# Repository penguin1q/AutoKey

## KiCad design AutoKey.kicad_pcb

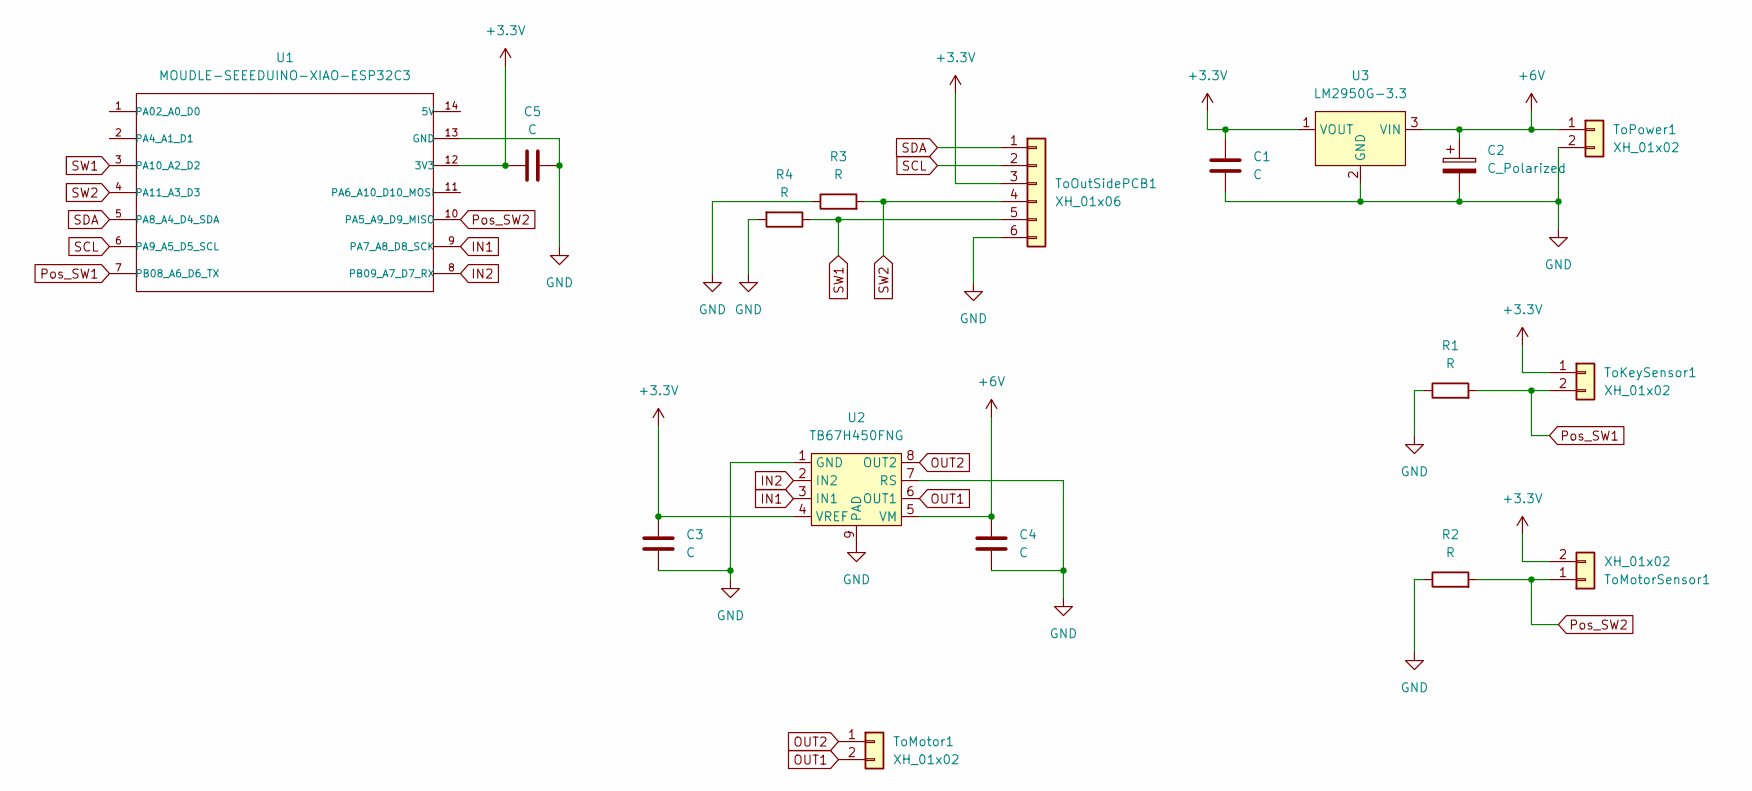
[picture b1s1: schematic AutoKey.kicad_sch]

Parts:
C1, C3, C4, C5: C; CP_EIA-1608-10_AVX-L_Pad1.25x1.05mm_HandSolder
C2: C_Polarized; CP_Radial_D5.0mm_P2.50mm
R1, R2, R3, R4: R; R_0603_1608Metric_Pad0.98x0.95mm_HandSolder
ToKeySensor1: XH_01x02; JST_XH_S2B-XH-A_1x02_P2.50mm_Horizontal
ToMotor1: XH_01x02; JST_XH_S2B-XH-A_1x02_P2.50mm_Horizontal
ToMotorSensor1: XH_01x02; JST_XH_S2B-XH-A_1x02_P2.50mm_Horizontal
ToOutSidePCB1: XH_01x06; JST_XH_S6B-XH-A_1x06_P2.50mm_Horizontal
ToPower1: XH_01x02; JST_XH_S2B-XH-A_1x02_P2.50mm_Horizontal
U1: MOUDLE-SEEEDUINO-XIAO-ESP32C3; MOUDLE14P-SMD-2.54-21X17.8MM
U2: TB67H450FNG; HSOP-8-1EP_3.9x4.9mm_P1.27mm_EP2.3x2.3mm_ThermalVias
U3: LM2950G-3.3; TO-92_Inline

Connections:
+3.3V: C1.2, C3.2, C5.2, ToKeySensor1.1, ToMotorSensor1.2, ToOutSidePCB1.3, U1.12 (3V3), U2.4 (VREF), U3.1 (VOUT)
+6V: C2.1, C4.2, ToPower1.1, U2.5 (VM), U3.3 (VIN)
GND: C1.1, C2.2, C3.1, C4.1, C5.1, R1.1, R2.1, R3.1, R4.2, ToOutSidePCB1.6, ToPower1.2, U1.13 (GND), U2.1 (GND), U2.7 (RS), U2.9 (PAD), U3.2 (GND)
IN1: U1.9 (PA7_A8_D8_SCK), U2.3 (IN1)
IN2: U1.8 (PB09_A7_D7_RX), U2.2 (IN2)
OUT1: ToMotor1.2, U2.6 (OUT1)
OUT2: ToMotor1.1, U2.8 (OUT2)
Pos_SW1: R1.2, ToKeySensor1.2, U1.7 (PB08_A6_D6_TX)
Pos_SW2: R2.2, ToMotorSensor1.1, U1.10 (PA5_A9_D9_MISO)
SCL: ToOutSidePCB1.2, U1.6 (PA9_A5_D5_SCL)
SDA: ToOutSidePCB1.1, U1.5 (PA8_A4_D4_SDA)
SW1: R4.1, ToOutSidePCB1.5, U1.3 (PA10_A2_D2)
SW2: R3.2, ToOutSidePCB1.4, U1.4 (PA11_A3_D3)

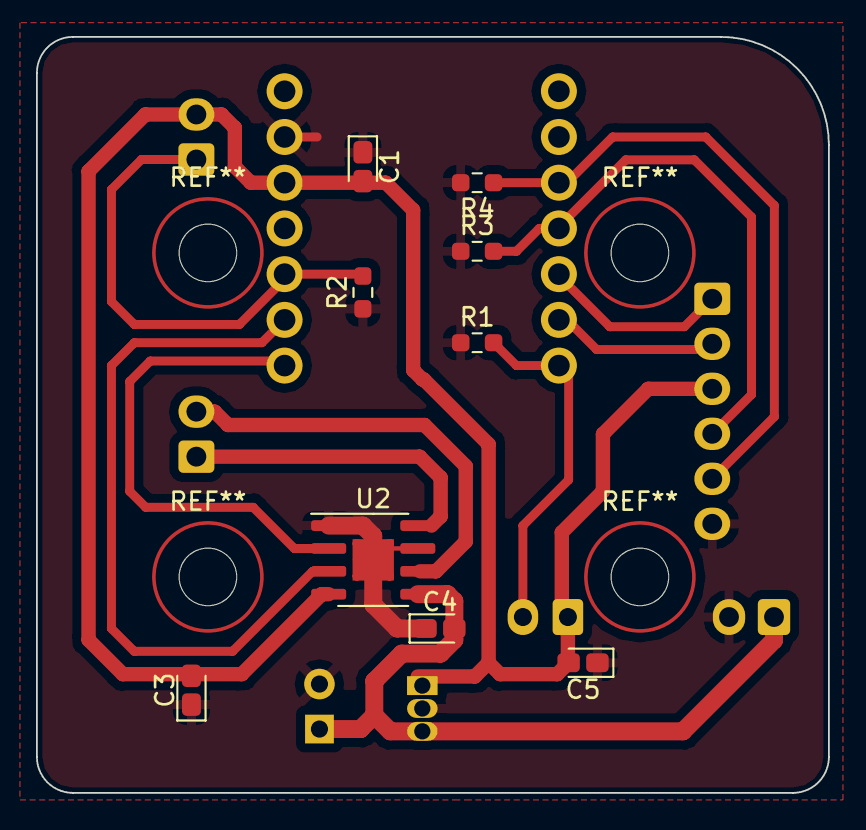
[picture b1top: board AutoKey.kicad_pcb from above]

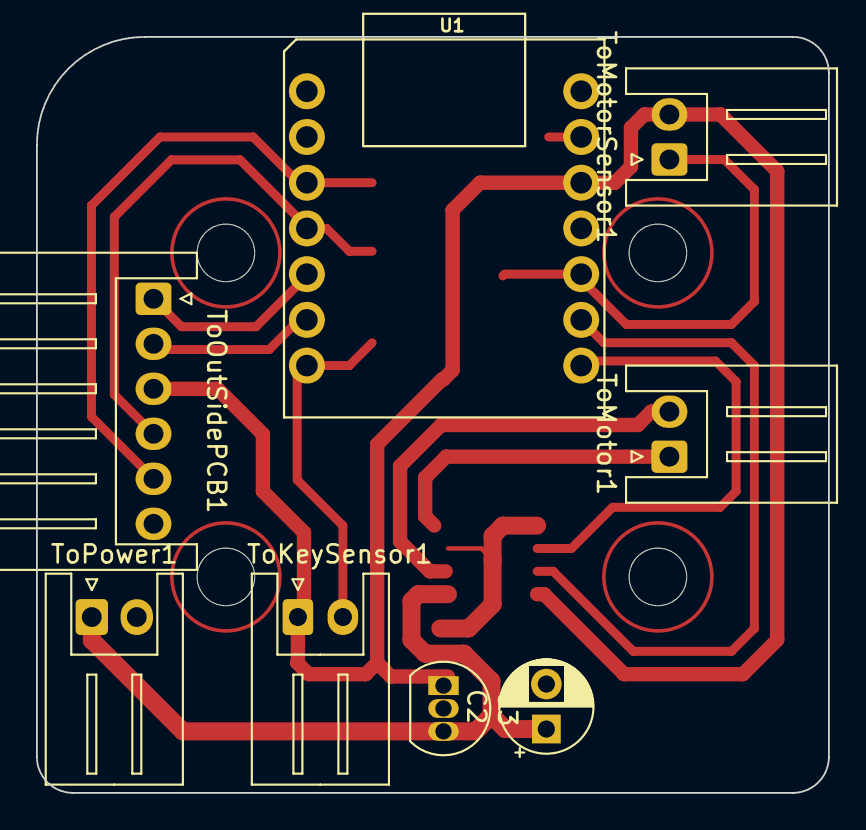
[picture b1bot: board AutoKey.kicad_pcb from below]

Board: 2 copper layers, 44.0 x 42.0 mm, 17 parts (8 on the bottom side), 13 nets.
